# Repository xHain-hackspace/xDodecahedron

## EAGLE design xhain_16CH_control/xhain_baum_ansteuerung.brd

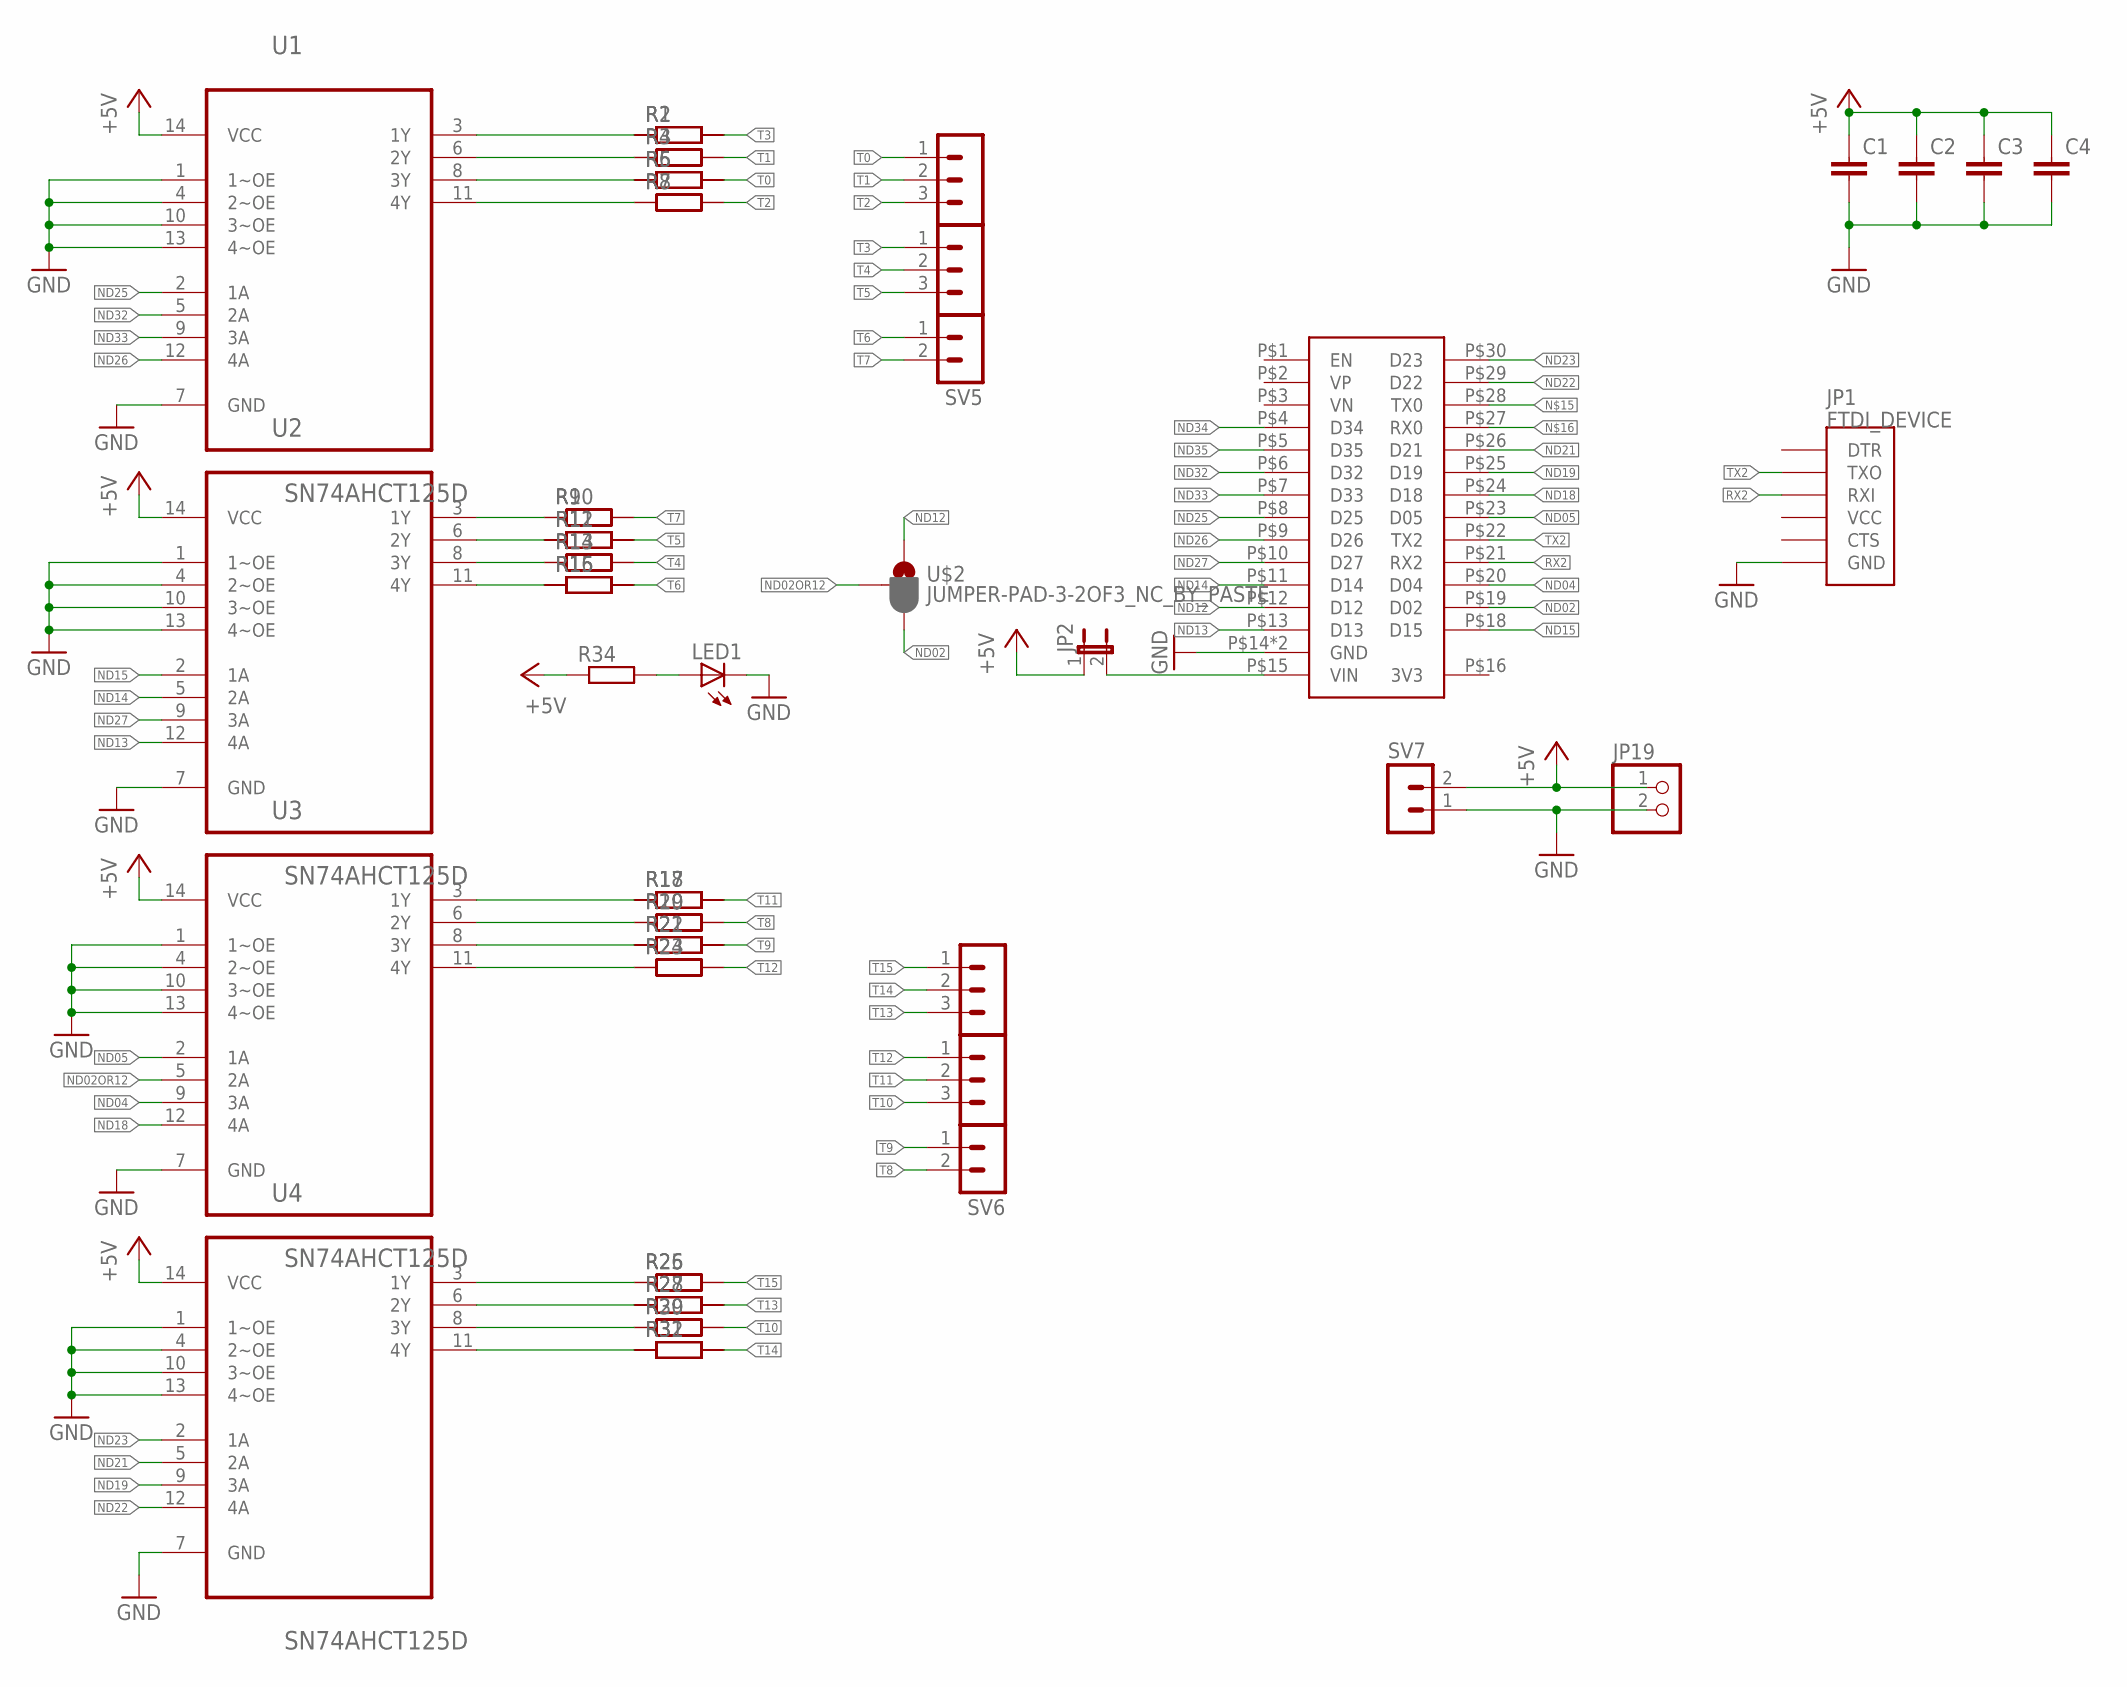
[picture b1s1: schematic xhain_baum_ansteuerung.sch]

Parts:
C1, C2, C3, C4: C5/2.5; C5B2.5
JP1: FTDI_DEVICE; FTDI_DEVICE_SIDE
JP2: JP1E; JP1
JP19: PINHD-1X2; 1X02
LED1: LED5MM
R1, R3, R5, R7, R9, R11, R13, R15, R17, R19, R21, R23, R25, R27, R29, R31, R34: R-EU_0204/7_BIG; 0204/7_BIG
R2, R4, R6, R8, R10, R12, R14, R16, R18, R20, R22, R24, R26, R28, R30, R32: R-EU_R1206; R1206
SV1, SV2, SV3, SV4: MA03-1
SV5, SV6, SV7: MA02-1
U1, U2, U3, U4: SN74AHCT125D; DIP254P762X508-14
U$1: ESP32_DEVKIT_V1
U$2: JUMPER-PAD-3-2OF3_NC_BY_PASTE; PAD-JUMPER-3-2OF3_NC_BY_PASTE_YES_SILK_FULL_BOX

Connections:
1_1Y: R1.1, R2.1, U1.3 (1Y)
1_2Y: R3.1, R4.1, U1.6 (2Y)
1_3Y: R5.1, R6.1, U1.8 (3Y)
1_4Y: R7.1, R8.1, U1.11 (4Y)
2_1Y: R9.1, R10.1, U2.3 (1Y)
2_2Y: R11.1, R12.1, U2.6 (2Y)
2_3Y: R13.1, R14.1, U2.8 (3Y)
2_4Y: R15.1, R16.1, U2.11 (4Y)
3_1Y: R17.1, R18.1, U3.3 (1Y)
3_2Y: R19.1, R20.1, U3.6 (2Y)
3_3Y: R21.1, R22.1, U3.8 (3Y)
3_4Y: R23.1, R24.1, U3.11 (4Y)
4_1Y: R25.1, R26.1, U4.3 (1Y)
4_2Y: R27.1, R28.1, U4.6 (2Y)
4_3Y: R29.1, R30.1, U4.8 (3Y)
4_4Y: R31.1, R32.1, U4.11 (4Y)
+5V: C1.1, C2.1, C3.1, C4.1, JP2.1, JP19.1, R34.1, SV7.2, U1.14 (VCC), U2.14 (VCC), U3.14 (VCC), U4.14 (VCC)
GND: C1.2, C2.2, C3.2, C4.2, JP1.P$6 (GND), JP19.2, LED1.K (C), SV7.1, U1.1 (1~OE), U1.4 (2~OE), U1.7 (GND), U1.10 (3~OE), U1.13 (4~OE), U2.1 (1~OE), U2.4 (2~OE), U2.7 (GND), U2.10 (3~OE), U2.13 (4~OE), U3.1 (1~OE), U3.4 (2~OE), U3.7 (GND), U3.10 (3~OE), U3.13 (4~OE), U4.1 (1~OE), U4.4 (2~OE), U4.7 (GND), U4.10 (3~OE), U4.13 (4~OE), U$1.P$14 (GND), U$1.P$17 (GND)
unnamed: LED1.A, R34.2
unnamed: JP2.2, U$1.P$15 (VIN)
ND02: U$1.P$19 (D02), U$2.3
ND02OR12: U3.5 (2A), U$2.2
ND04: U3.9 (3A), U$1.P$20 (D04)
ND05: U3.2 (1A), U$1.P$23 (D05)
ND12: U$1.P$12 (D12), U$2.1
ND13: U2.12 (4A), U$1.P$13 (D13)
ND14: U2.5 (2A), U$1.P$11 (D14)
ND15: U2.2 (1A), U$1.P$18 (D15)
ND18: U3.12 (4A), U$1.P$24 (D18)
ND19: U4.9 (3A), U$1.P$25 (D19)
ND21: U4.5 (2A), U$1.P$26 (D21)
ND22: U4.12 (4A), U$1.P$29 (D22)
ND23: U4.2 (1A), U$1.P$30 (D23)
ND25: U1.2 (1A), U$1.P$8 (D25)
ND26: U1.12 (4A), U$1.P$9 (D26)
ND27: U2.9 (3A), U$1.P$10 (D27)
ND32: U1.5 (2A), U$1.P$6 (D32)
ND33: U1.9 (3A), U$1.P$7 (D33)
ND34: U$1.P$4 (D34)
ND35: U$1.P$5 (D35)
RX2: JP1.P$3 (RXI), U$1.P$21 (RX2)
T0: R5.2, R6.2, SV1.1
T1: R3.2, R4.2, SV1.2
T2: R7.2, R8.2, SV1.3
T3: R1.2, R2.2, SV2.1
T4: R13.2, R14.2, SV2.2
T5: R11.2, R12.2, SV2.3
T6: R15.2, R16.2, SV5.1
T7: R9.2, R10.2, SV5.2
T8: R19.2, R20.2, SV6.2
T9: R21.2, R22.2, SV6.1
T10: R29.2, R30.2, SV4.3
T11: R17.2, R18.2, SV4.2
T12: R23.2, R24.2, SV4.1
T13: R27.2, R28.2, SV3.3
T14: R31.2, R32.2, SV3.2
T15: R25.2, R26.2, SV3.1
TX2: JP1.P$2 (TXO), U$1.P$22 (TX2)

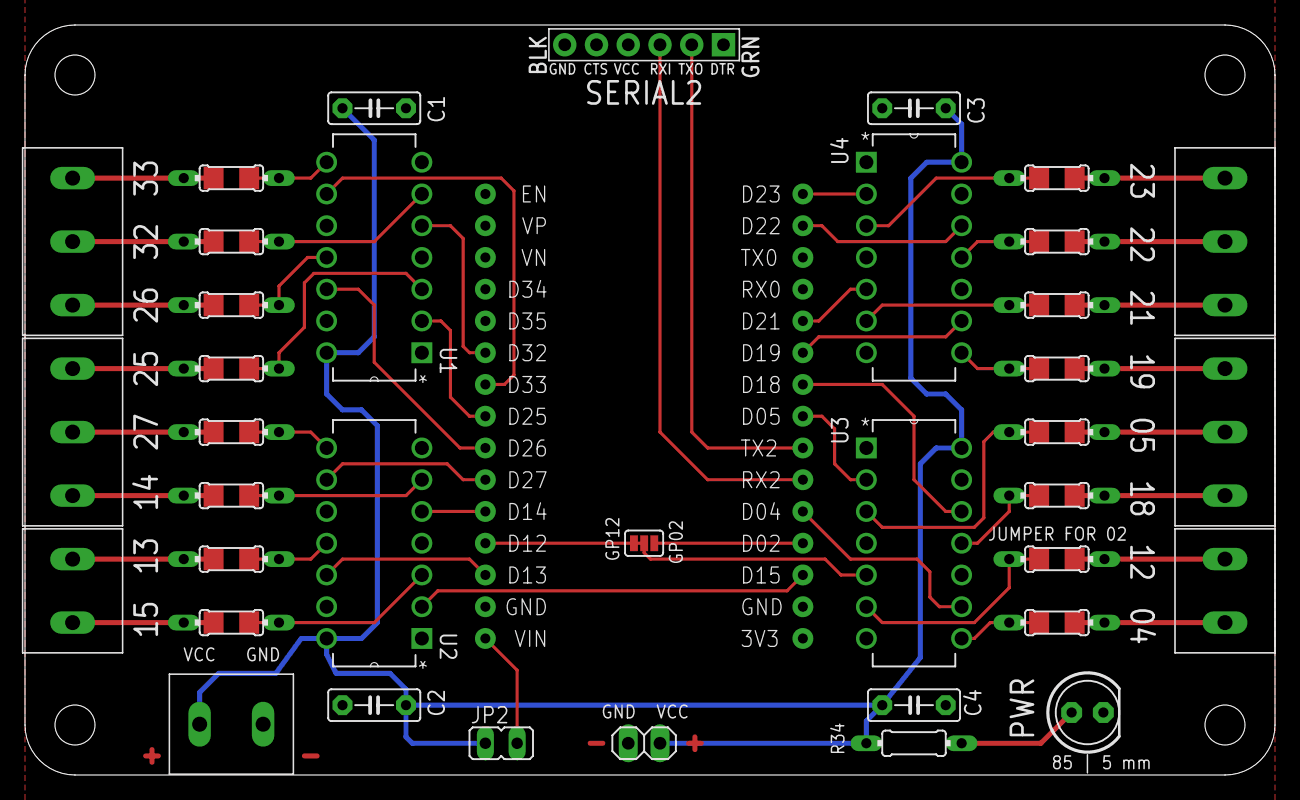
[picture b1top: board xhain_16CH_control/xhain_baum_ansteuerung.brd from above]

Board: 2 copper layers, 100.0 x 60.0 mm, 54 parts (0 on the bottom side), 56 nets.

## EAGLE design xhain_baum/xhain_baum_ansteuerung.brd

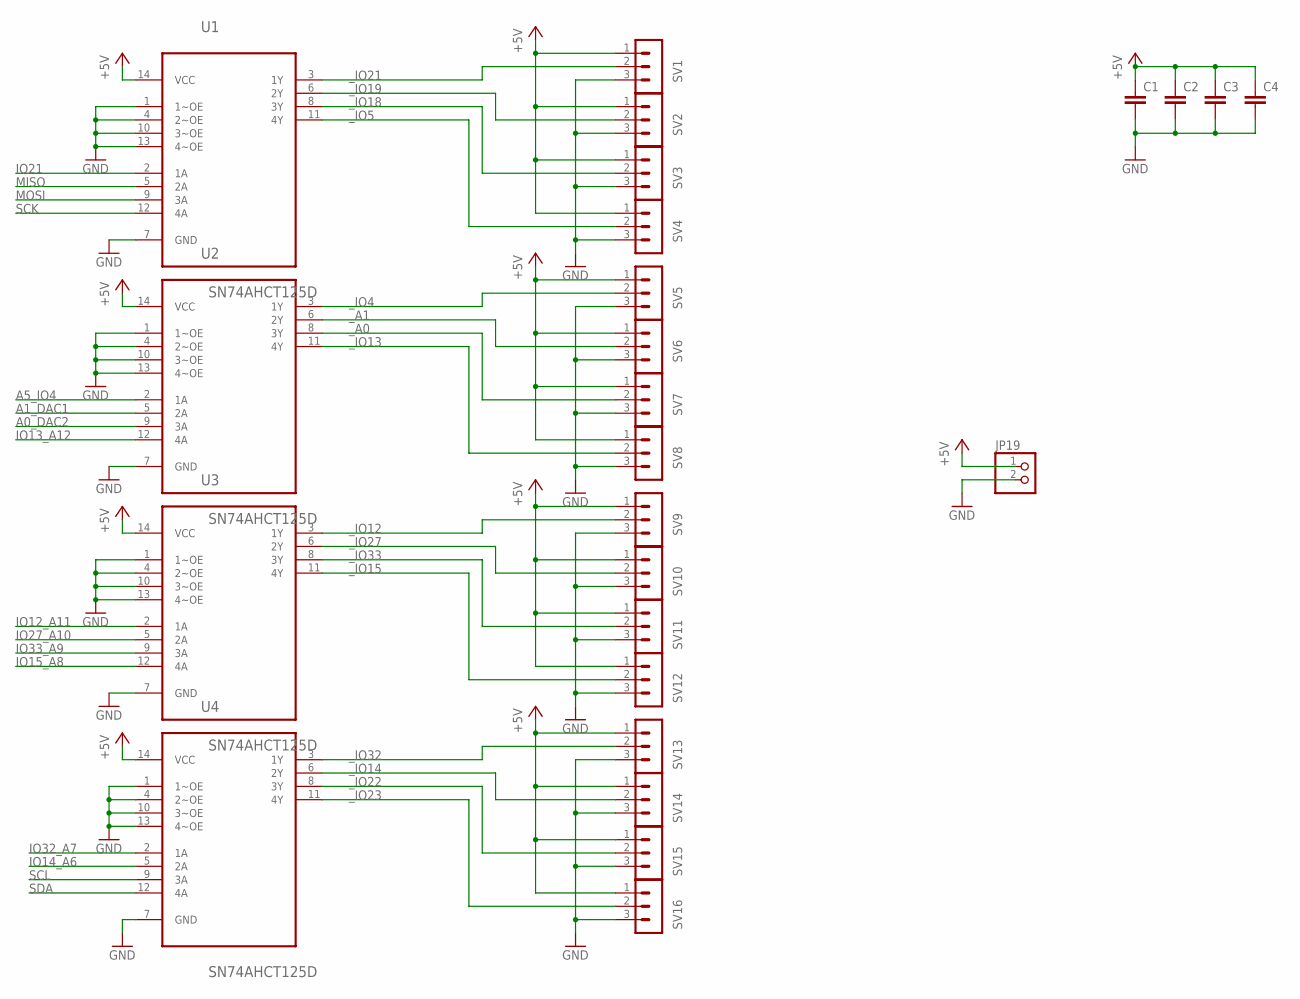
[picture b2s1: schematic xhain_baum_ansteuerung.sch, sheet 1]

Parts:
C1, C2, C3, C4: C5/2.5; C5B2.5
JP19: PINHD-1X2; 1X02
SV1, SV2, SV3, SV4, SV5, SV6, SV7, SV8, SV9, SV10, SV11, SV12, SV13, SV14, SV15, SV16: MA03-1
U1, U2, U3, U4: SN74AHCT125D; DIP254P762X508-14

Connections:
+5V: C1.1, C2.1, C3.1, C4.1, JP19.1, SV1.1, SV2.1, SV3.1, SV4.1, SV5.1, SV6.1, SV7.1, SV8.1, SV9.1, SV10.1, SV11.1, SV12.1, SV13.1, SV14.1, SV15.1, SV16.1, U1.14 (VCC), U2.14 (VCC), U3.14 (VCC), U4.14 (VCC)
A0_DAC2: U2.9 (3A); also elsewhere on the board
A1_DAC1: U2.5 (2A); also elsewhere on the board
A5_IO4: U2.2 (1A); also elsewhere on the board
GND: C1.2, C2.2, C3.2, C4.2, JP19.2, SV1.3, SV2.3, SV3.3, SV4.3, SV5.3, SV6.3, SV7.3, SV8.3, SV9.3, SV10.3, SV11.3, SV12.3, SV13.3, SV14.3, SV15.3, SV16.3, U1.1 (1~OE), U1.4 (2~OE), U1.7 (GND), U1.10 (3~OE), U1.13 (4~OE), U2.1 (1~OE), U2.4 (2~OE), U2.7 (GND), U2.10 (3~OE), U2.13 (4~OE), U3.1 (1~OE), U3.4 (2~OE), U3.7 (GND), U3.10 (3~OE), U3.13 (4~OE), U4.1 (1~OE), U4.4 (2~OE), U4.7 (GND), U4.10 (3~OE), U4.13 (4~OE); also elsewhere on the board
IO12_A11: U3.2 (1A); also elsewhere on the board
IO13_A12: U2.12 (4A); also elsewhere on the board
IO14_A6: U4.5 (2A); also elsewhere on the board
IO15_A8: U3.12 (4A); also elsewhere on the board
IO21: U1.2 (1A); also elsewhere on the board
IO27_A10: U3.5 (2A); also elsewhere on the board
IO32_A7: U4.2 (1A); also elsewhere on the board
IO33_A9: U3.9 (3A); also elsewhere on the board
MISO: U1.5 (2A); also elsewhere on the board
MOSI: U1.9 (3A); also elsewhere on the board
SCK: U1.12 (4A); also elsewhere on the board
SCL: U4.9 (3A); also elsewhere on the board
SDA: U4.12 (4A); also elsewhere on the board
_A0: SV7.2, U2.8 (3Y)
_A1: SV6.2, U2.6 (2Y)
_IO4: SV5.2, U2.3 (1Y)
_IO5: SV4.2, U1.11 (4Y)
_IO12: SV9.2, U3.3 (1Y)
_IO13: SV8.2, U2.11 (4Y)
_IO14: SV14.2, U4.6 (2Y)
_IO15: SV12.2, U3.11 (4Y)
_IO18: SV3.2, U1.8 (3Y)
_IO19: SV2.2, U1.6 (2Y)
_IO21: SV1.2, U1.3 (1Y)
_IO22: SV15.2, U4.8 (3Y)
_IO23: SV16.2, U4.11 (4Y)
_IO27: SV10.2, U3.6 (2Y)
_IO32: SV13.2, U4.3 (1Y)
_IO33: SV11.2, U3.8 (3Y)

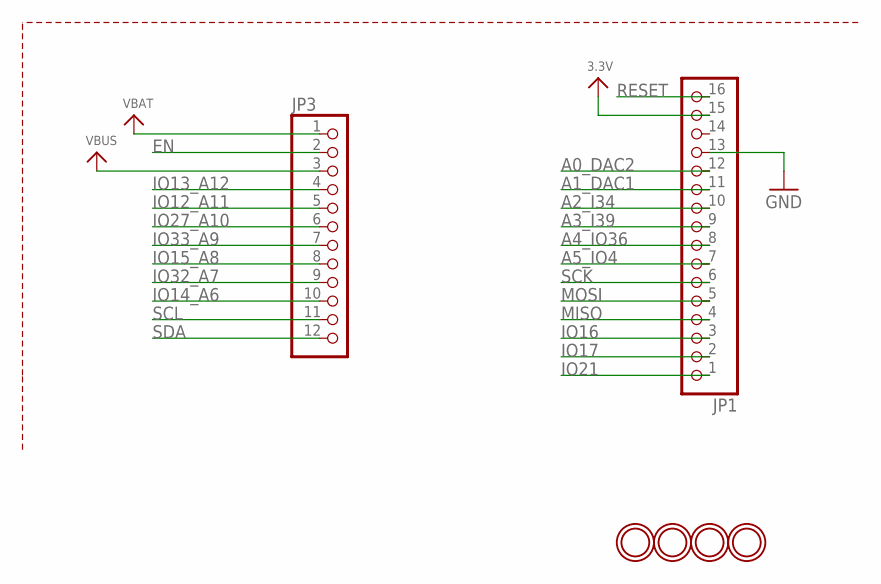
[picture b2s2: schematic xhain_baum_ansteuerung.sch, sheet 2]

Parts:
JP1: HEADER-1X16_MIN; 1X16_ROUND_MIN
JP3: HEADER-1X12_MIN; 1X12_ROUND_MIN
U$1, U$2, U$31, U$32: MOUNTINGHOLE2.5; MOUNTINGHOLE_2.5_PLATED

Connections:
3.3V: JP1.15
A0_DAC2: JP1.12; also elsewhere on the board
A1_DAC1: JP1.11; also elsewhere on the board
A2_I34: JP1.10
A3_I39: JP1.9
A4_IO36: JP1.8
A5_IO4: JP1.7; also elsewhere on the board
EN: JP3.2
GND: JP1.13; also elsewhere on the board
IO12_A11: JP3.5; also elsewhere on the board
IO13_A12: JP3.4; also elsewhere on the board
IO14_A6: JP3.10; also elsewhere on the board
IO15_A8: JP3.8; also elsewhere on the board
IO16: JP1.3
IO17: JP1.2
IO21: JP1.1; also elsewhere on the board
IO27_A10: JP3.6; also elsewhere on the board
IO32_A7: JP3.9; also elsewhere on the board
IO33_A9: JP3.7; also elsewhere on the board
MISO: JP1.4; also elsewhere on the board
MOSI: JP1.5; also elsewhere on the board
RESET: JP1.16
SCK: JP1.6; also elsewhere on the board
SCL: JP3.11; also elsewhere on the board
SDA: JP3.12; also elsewhere on the board
VBAT: JP3.1
VBUS: JP3.3

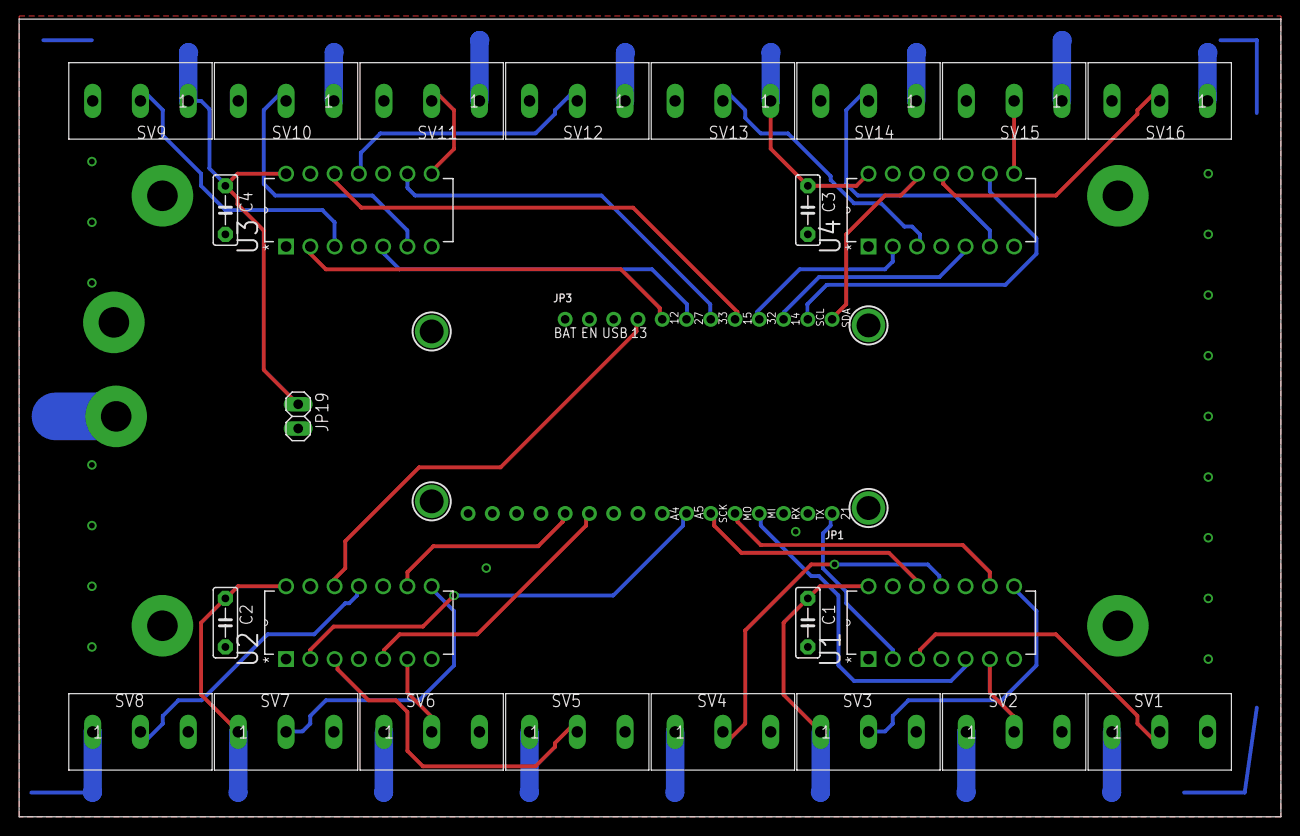
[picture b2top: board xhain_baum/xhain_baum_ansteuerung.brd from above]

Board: 2 copper layers, 132.1 x 83.5 mm, 31 parts (0 on the bottom side), 34 nets.

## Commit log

2019-07-07 List of all required materials to build the big dodecahedron
2019-07-08 kleiner-dode
2019-07-08 added PCB Layoutfor control
2019-07-08 rename
2019-07-08 added todo
2019-07-24 schmalere Platine
2019-07-24 board preview
2019-07-24 pin fu
2019-07-24 sheesh
2020-02-04 das ist der Aufbau der einzelnen Kanten mit Richtung der Daten und Nummerierung
2020-02-04 Aufbau und Datenrichtung der LED Kanten
2021-01-22 add jumper to connect 5V to ESP32

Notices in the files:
parts and their libraries:
SparkFun-Connectors: Licensing: Creative Commons ShareAlike 4.0 International - https://creativecommons.org/licenses/by-sa/4.0
microbuilder: This work is placed in the public domain, and may be freely used for commercial and non-commercial work with the following conditions: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
